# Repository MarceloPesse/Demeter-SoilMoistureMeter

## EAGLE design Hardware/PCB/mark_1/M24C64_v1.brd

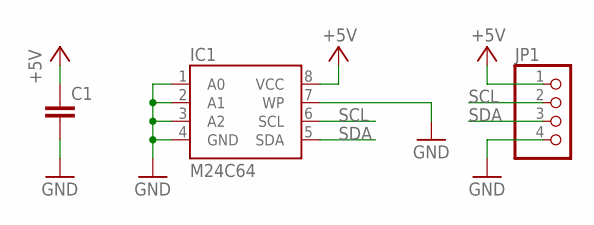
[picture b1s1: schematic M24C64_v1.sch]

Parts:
C1: C-EUC0805K; C0805K
IC1: M24C64; SO08
JP1: PINHD-1X4; 1X04

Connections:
+5V: C1.1, IC1.8 (VCC), JP1.1
GND: C1.2, IC1.1 (A0), IC1.2 (A1), IC1.3 (A2), IC1.4 (GND), IC1.7 (WP), JP1.4
SCL: IC1.6 (SCL), JP1.2
SDA: IC1.5 (SDA), JP1.3

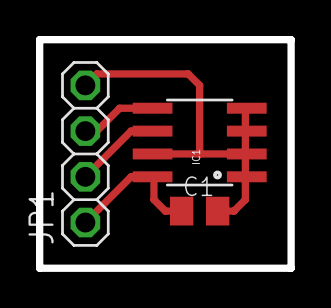
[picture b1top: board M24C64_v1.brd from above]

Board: 2 copper layers, 14.0 x 12.7 mm, 3 parts (0 on the bottom side), 4 nets.

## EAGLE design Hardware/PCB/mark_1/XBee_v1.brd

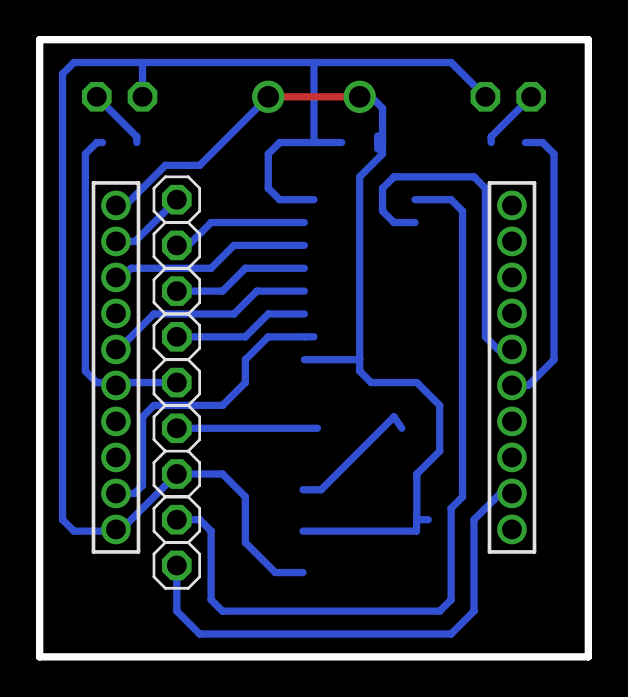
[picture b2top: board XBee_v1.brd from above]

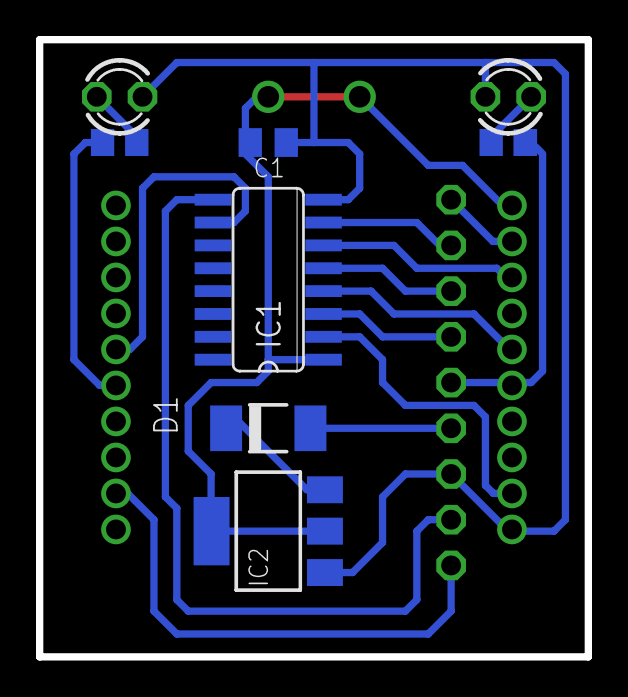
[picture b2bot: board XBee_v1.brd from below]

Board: 2 copper layers, 30.5 x 34.3 mm, 17 parts (8 on the bottom side), 18 nets.

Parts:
C1: 100nF; C0805K
D1: S1M; DO-214AC
IC1: 4050; SO16
IC2: LM1117S; SOT223
IC3: XBEE-1B1; XBEE-1
JP1: 1X02
JP2: TXD; 1X01
JP3: RXD; 1X01
JP4: RST; 1X01
JP5: RSSI; 1X01
JP6: DTR; 1X01
JP7: CTS; 1X01
JP8: RTS; 1X01
LED1, LED2: LED3MM
R1, R2: R0805

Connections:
+3V3: C1.2, IC1.1, IC2.2, IC2.4, IC3.1
+5V: D1.A, JP1.1
CTS: IC3.12, JP7.1
DTR: IC1.3, JP6.1
GND: C1.1, IC1.8, IC2.1, IC3.10, JP1.2, LED1.K, LED2.K
unnamed: D1.C, IC2.3
unnamed: IC1.6, IC3.3
unnamed: IC1.4, IC3.5
unnamed: LED1.A, R1.1
unnamed: IC1.2, IC3.9
unnamed: IC1.10, IC3.16
unnamed: LED2.A, R2.1
unnamed: IC3.15, R2.2
RESET: IC1.5, JP4.1
RSSI: IC3.6, JP5.1, R1.2
RTS: IC1.9, JP8.1
RXD: IC1.7, JP3.1
TXD: IC3.2, JP2.1

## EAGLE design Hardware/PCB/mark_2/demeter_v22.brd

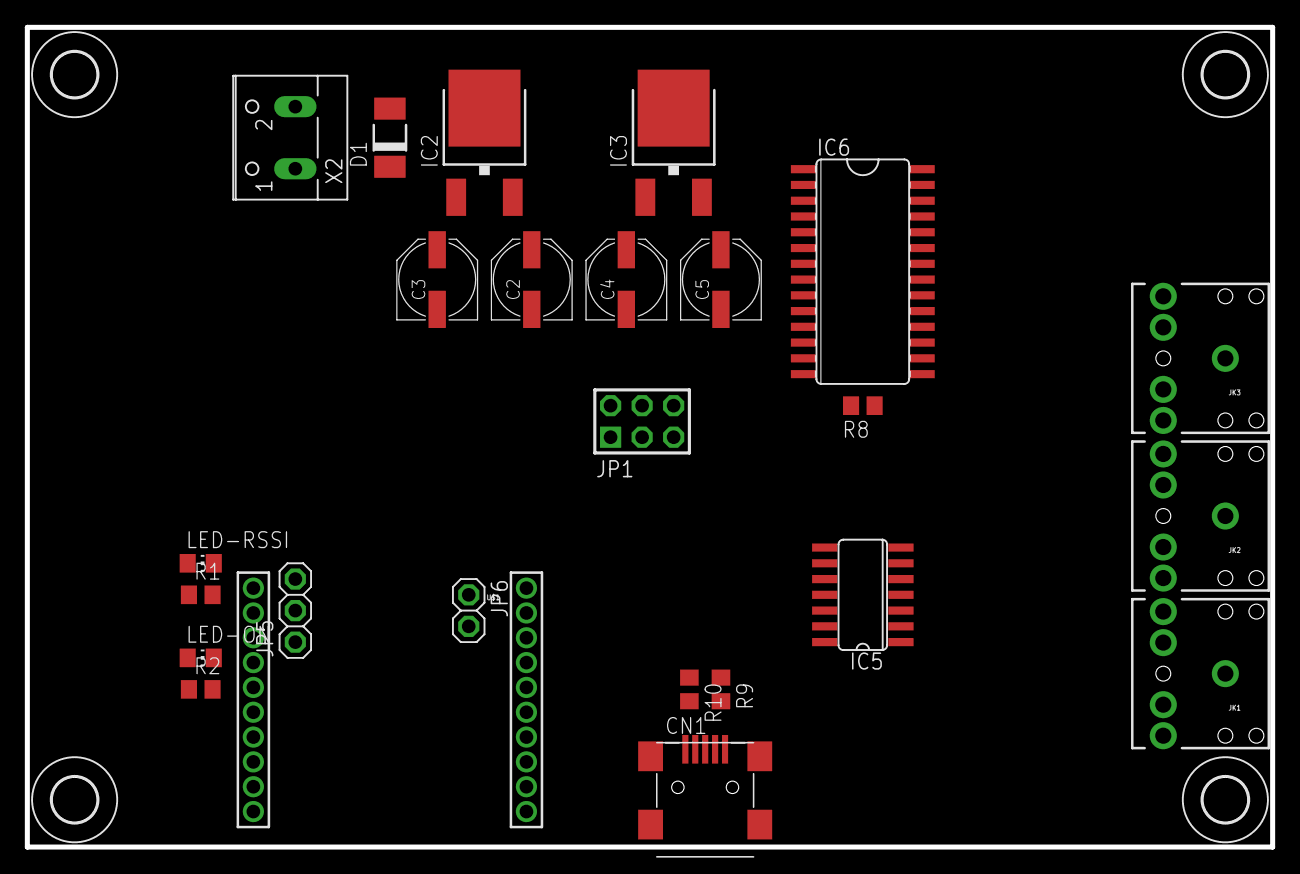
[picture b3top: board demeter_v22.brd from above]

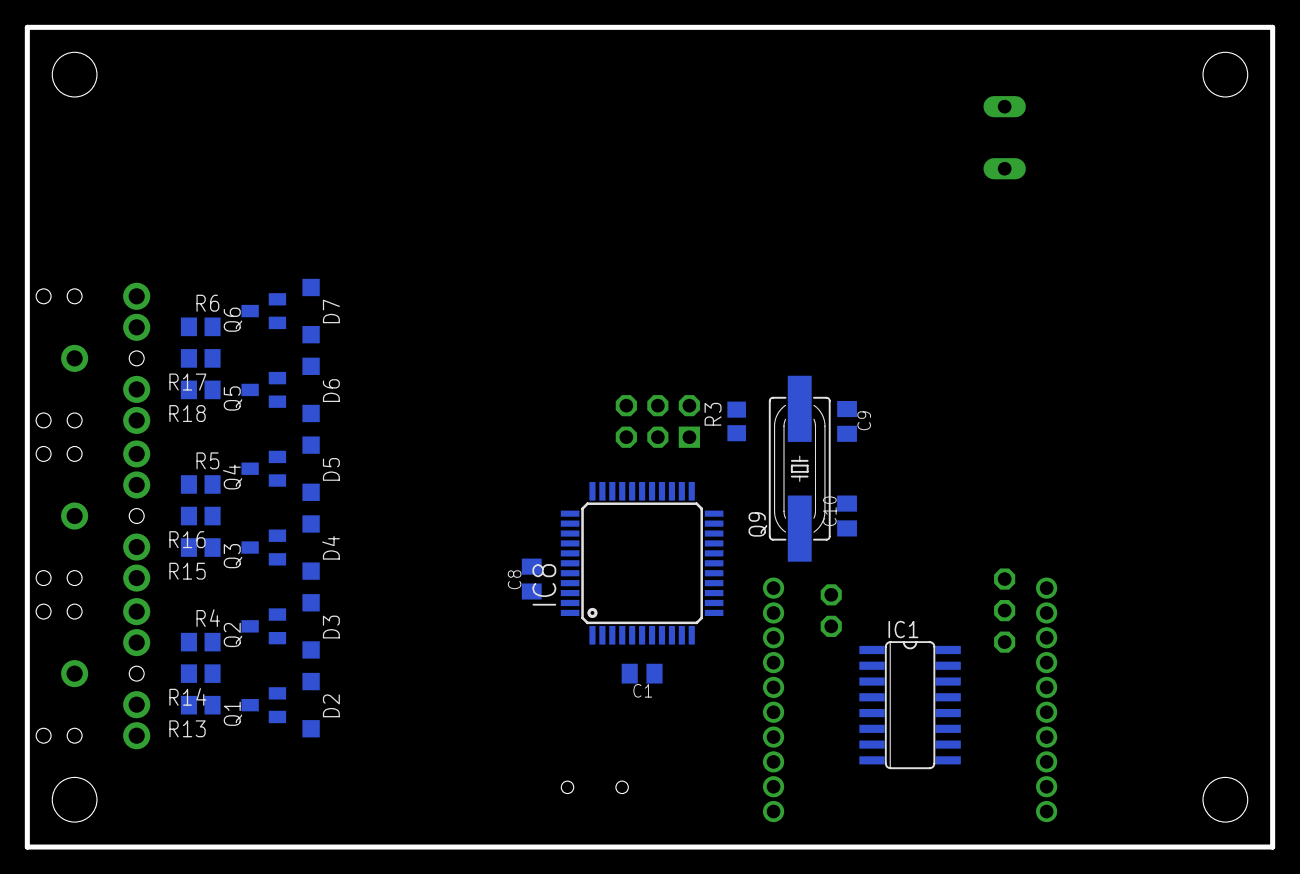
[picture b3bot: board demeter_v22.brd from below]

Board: 2 copper layers, 100.3 x 66.0 mm, 58 parts (29 on the bottom side), 55 nets, no tracks yet.

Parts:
C1: 1uF; C0805K
C2, C4: 22uF; PANASONIC_D
C3, C5: 100uF; PANASONIC_D
C8: 100nF; C0805K
C9, C10: 22pF; C0805K
CN1: USB-MINIB
D1: S1M; DO-214AC
D2, D3, D4, D5, D6, D7: SOD123
IC1: 4050; SO16
IC2: LM1117-5.0; DPACK
IC3: LM1117-3.3; DPACK
IC5: MCP3424; SO14
IC6: MCP23017SO; SO28W
IC8: ATMEGA32U4-AU; TQFP44
JK1, JK2, JK3: AUDIO-JACK
JP1: AVR-ISP-6
JP5: 1X03
JP6: 1X02
LED-ON: CHIP-LED0805
LED-RSSI: CHIP-LED0805
Q1, Q3, Q5: IRLML6402; SOT23
Q2, Q4, Q6: SOT23
Q9: HC49UP
R1, R2, R3, R4, R5, R6, R8, R13, R14, R15, R16, R17, R18: R0805
R9, R10: 22; R0805
U$1: XBEE-1B1; XBEE-1
U$2, U$3, U$4, U$5: 3,6
X2: W237-102

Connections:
+3V3: C5.+, D3.A, D5.A, D7.A, IC1.1, IC3.4, U$1.1
+5V: C3.+, D2.A, D4.A, D6.A, IC2.4, IC5.6, IC6.9, IC8.2, IC8.14, IC8.24, IC8.34, IC8.44, JP1.2, JP6.1, R3.2, R8.2
+12V: C2.+, C4.+, D1.C, IC2.3, IC3.3
CH1: IC5.1, R13.1, R14.1
CH2: IC5.3, R15.1, R16.1
CH3: IC5.11, R17.1, R18.1
D+: IC8.4, R9.1
D-: IC8.3, R10.1
EN1-3: IC6.22, Q2.1
EN1-5: IC6.21, Q1.1
EN2-3: IC6.24, Q4.1
EN2-5: IC6.23, Q3.1
EN3-3: IC6.26, Q6.1
EN3-5: IC6.25, Q5.1
GND: C1.2, C2.-, C3.-, C4.-, C5.-, C8.2, C9.2, C10.2, CN1.GND, IC1.8, IC2.1, IC3.1, IC5.2, IC5.4, IC5.5, IC5.9, IC5.10, IC5.12, IC5.14, IC6.10, IC6.15, IC6.16, IC6.17, IC8.5, IC8.15, IC8.23, IC8.33, IC8.35, IC8.43, JK1.SLEEVE, JK2.SLEEVE, JK3.SLEEVE, JP1.6, JP6.2, LED-ON.C, LED-RSSI.C, R4.1, R5.1, R6.1, R14.2, R16.2, R17.2, U$1.10, X2.1
MISO: IC8.11, JP1.1
MOSI: IC8.10, JP1.4
unnamed: D1.A, X2.2
unnamed: IC1.6, U$1.3
unnamed: IC1.4, U$1.5
unnamed: LED-RSSI.A, R1.1
unnamed: IC1.2, U$1.9
unnamed: IC1.10, U$1.16
unnamed: LED-ON.A, R2.1
unnamed: R2.2, U$1.15
unnamed: IC6.18, R8.1
unnamed: JK1.TIP, Q1.3, Q2.3
unnamed: D2.C, Q1.2
unnamed: D3.C, Q2.2
unnamed: JK2.TIP, Q3.3, Q4.3
unnamed: D4.C, Q3.2
unnamed: D5.C, Q4.2
unnamed: JK3.TIP, Q5.3, Q6.3
unnamed: D6.C, Q5.2
unnamed: D7.C, Q6.2
unnamed: C1.1, IC8.6
unnamed: C8.1, IC8.42
unnamed: C9.1, IC8.17, Q9.2
unnamed: C10.1, IC8.16, Q9.1
unnamed: CN1.D+, R9.2
unnamed: CN1.D-, R10.2
unnamed: JK1.RING, R13.2
unnamed: JK2.RING, R15.2
unnamed: JK3.RING, R18.2
RSSI: R1.2, U$1.6
RST: IC8.13, JP1.5, R3.1
RX: IC8.20, JP5.1, U$1.2
SCK: IC8.9, JP1.3
SCL: IC5.8, IC6.12, IC8.18
SDA: IC5.7, IC6.13, IC8.19
SN1: IC6.4, JK1.TSH, R4.2
SN2: IC6.3, JK2.TSH, R5.2
SN3: IC6.2, JK3.TSH, R6.2
TX: IC1.7, IC8.21, JP5.3
VBUS: CN1.VBUS, IC8.7

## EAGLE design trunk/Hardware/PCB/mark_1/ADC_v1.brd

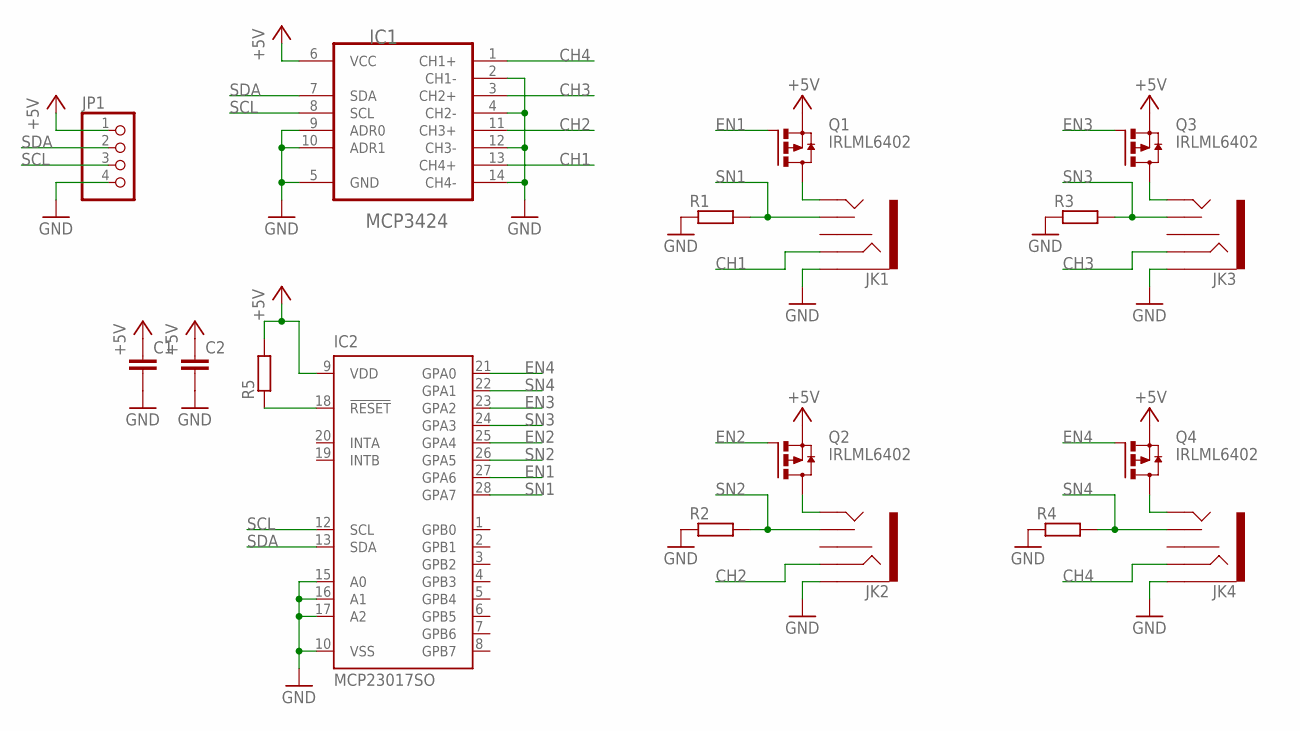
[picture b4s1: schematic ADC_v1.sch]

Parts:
C1, C2: C-EUC0805K; C0805K
IC1: MCP3424; SO14
IC2: MCP23017SO; SO28W
JK1, JK2, JK3, JK4: AUDIO-JACK2PTH; AUDIO-JACK
JP1: PINHD-1X4; 1X04
Q1, Q2, Q3, Q4: IRLML6402; SOT23
R1, R2, R3, R4, R5: R-EU_R0805; R0805

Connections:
+5V: C1.1, C2.1, IC1.6 (VCC), IC2.9 (VDD), JP1.1, Q1.2 (S), Q2.2 (S), Q3.2 (S), Q4.2 (S), R5.2
CH1: IC1.13 (CH4+), JK1.RING
CH2: IC1.11 (CH3+), JK2.RING
CH3: IC1.3 (CH2+), JK3.RING
CH4: IC1.1 (CH1+), JK4.RING
EN1: IC2.27 (GPA6), Q1.1 (G)
EN2: IC2.25 (GPA4), Q2.1 (G)
EN3: IC2.23 (GPA2), Q3.1 (G)
EN4: IC2.21 (GPA0), Q4.1 (G)
GND: C1.2, C2.2, IC1.2 (CH1-), IC1.4 (CH2-), IC1.5 (GND), IC1.9 (ADR0), IC1.10 (ADR1), IC1.12 (CH3-), IC1.14 (CH4-), IC2.10 (VSS), IC2.15 (A0), IC2.16 (A1), IC2.17 (A2), JK1.SLEEVE, JK2.SLEEVE, JK3.SLEEVE, JK4.SLEEVE, JP1.4, R1.1, R2.1, R3.1, R4.1
unnamed: JK1.TIP, Q1.3 (D)
unnamed: IC2.18 (!RESET), R5.1
unnamed: JK2.TIP, Q2.3 (D)
unnamed: JK3.TIP, Q3.3 (D)
unnamed: JK4.TIP, Q4.3 (D)
SCL: IC1.8 (SCL), IC2.12 (SCL), JP1.3
SDA: IC1.7 (SDA), IC2.13 (SDA), JP1.2
SN1: IC2.28 (GPA7), JK1.TSH, R1.2
SN2: IC2.26 (GPA5), JK2.TSH, R2.2
SN3: IC2.24 (GPA3), JK3.TSH, R3.2
SN4: IC2.22 (GPA1), JK4.TSH, R4.2

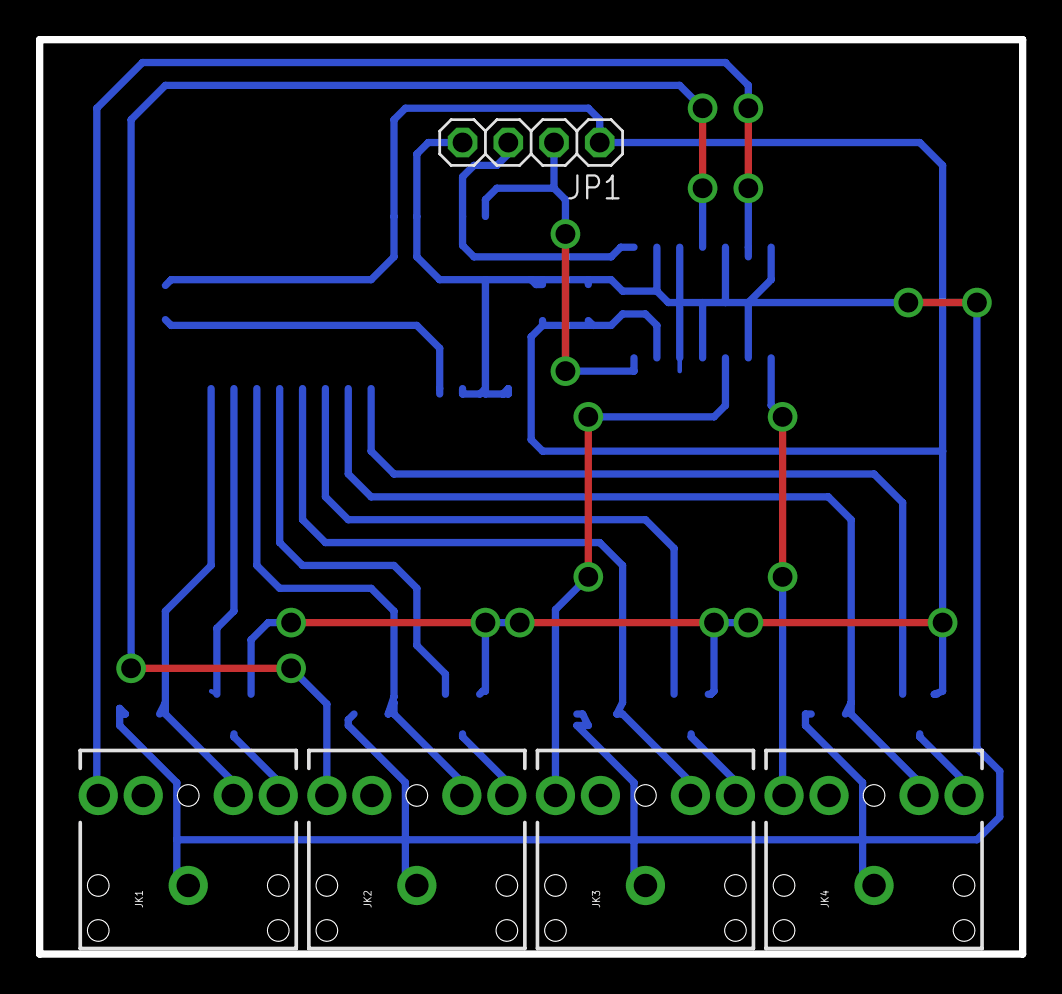
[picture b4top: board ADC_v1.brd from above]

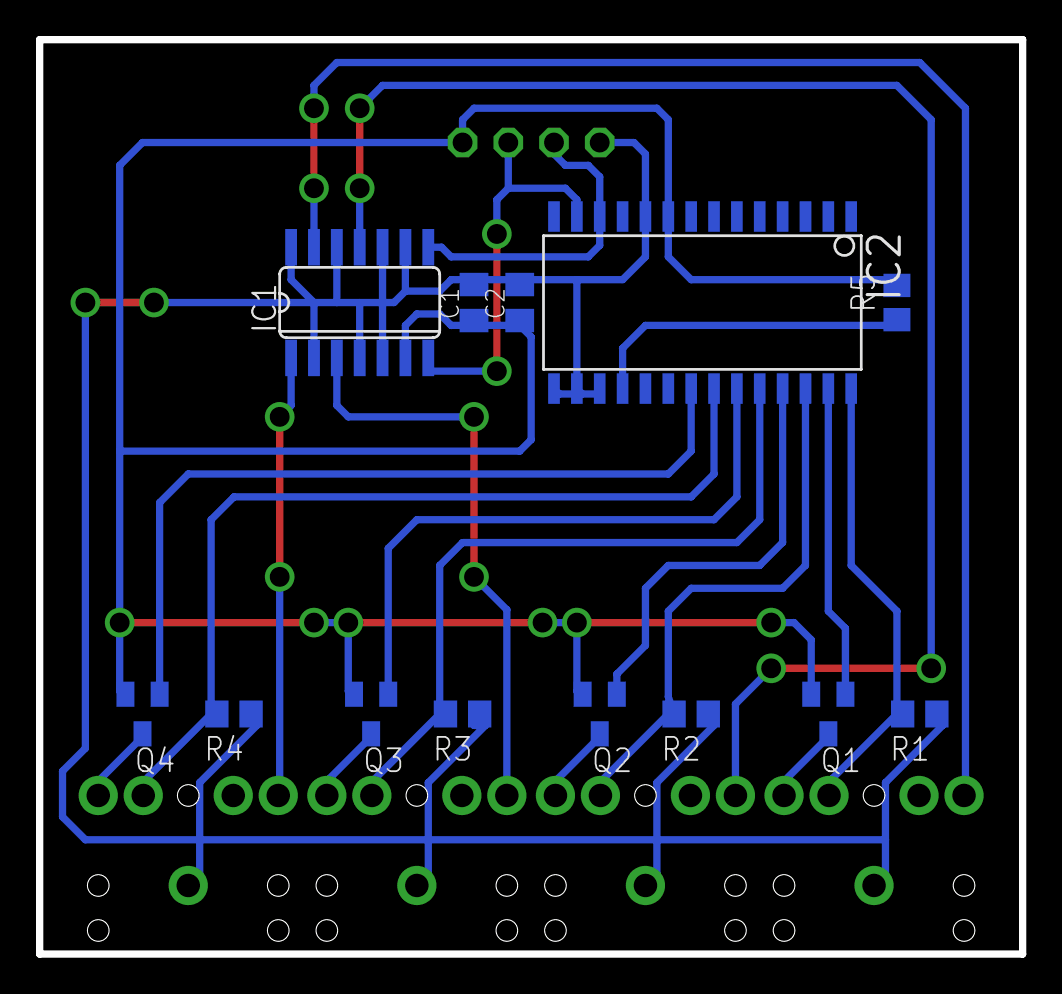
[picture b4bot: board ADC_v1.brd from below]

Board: 2 copper layers, 54.6 x 50.8 mm, 18 parts (13 on the bottom side), 21 nets.
